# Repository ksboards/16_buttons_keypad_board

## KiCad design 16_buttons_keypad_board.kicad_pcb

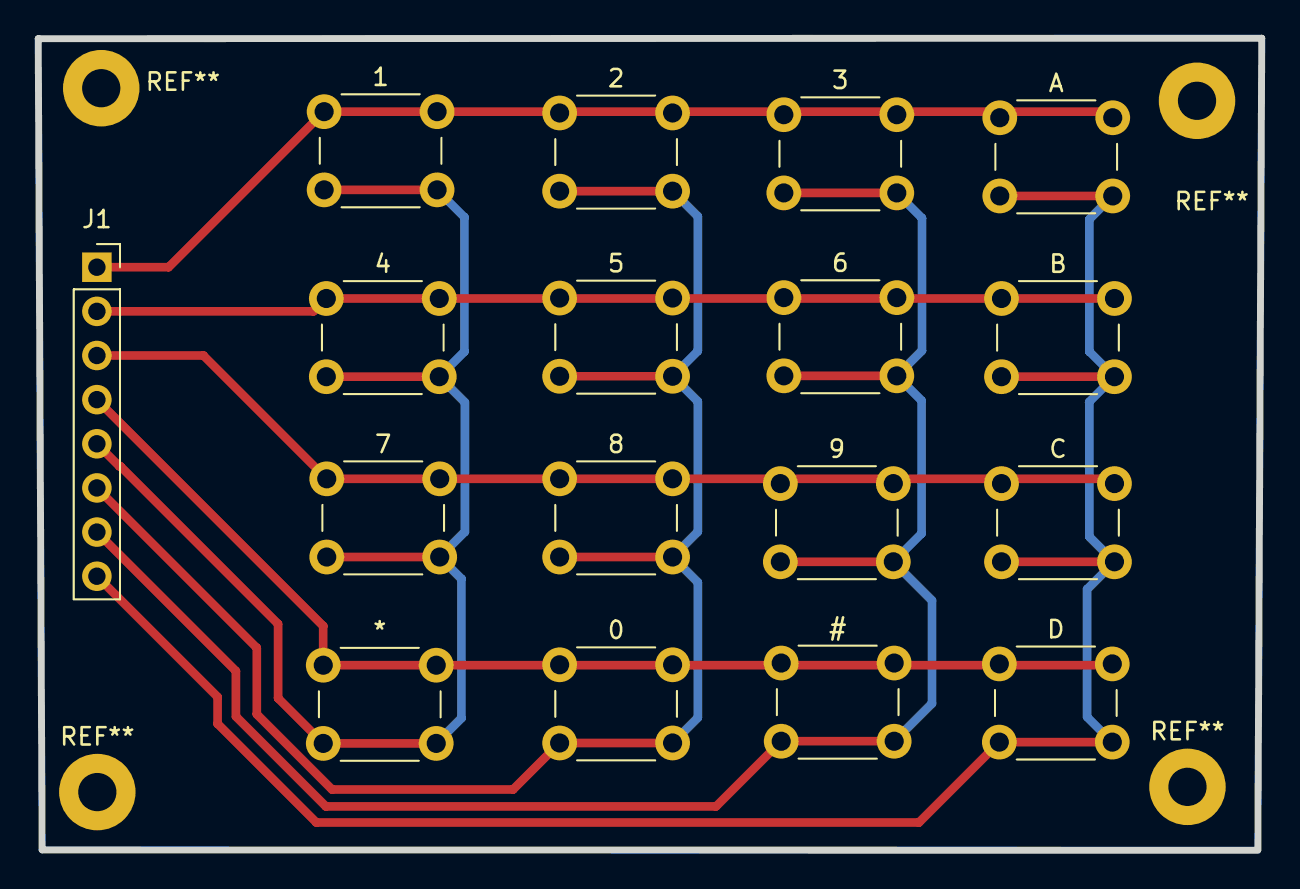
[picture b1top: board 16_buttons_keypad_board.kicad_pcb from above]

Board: 2 copper layers, 70.4 x 46.7 mm, 16 parts (0 on the bottom side), 8 nets.

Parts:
0, 1, 2, 3, 4, 5, 6, 7, 8, 9: SW_Push; SW_PUSH_6mm
*: SW_Push; SW_PUSH_6mm
A: SW_Push; SW_PUSH_6mm
B: SW_Push; SW_PUSH_6mm
C: SW_Push; SW_PUSH_6mm
D: SW_Push; SW_PUSH_6mm
J1: Conn_01x08; PinSocket_1x08_P2.54mm_Vertical

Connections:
/C1: 1.2, 4.2, 7.2, *.2, J1.5
/C2: 0.2, 2.2, 5.2, 8.2, J1.6
/C3: 3.2, 6.2, 9.2, J1.7
/C4: A.2, B.2, C.2, D.2, J1.8
/R1: 1.1, 2.1, 3.1, A.1, J1.1
/R2: 4.1, 5.1, 6.1, B.1, J1.2
/R3: 7.1, 8.1, 9.1, C.1, J1.3
/R4: 0.1, *.1, D.1, J1.4

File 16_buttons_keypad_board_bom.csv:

"Id";"Référence";"Boîtier";"Quantité";"Désignation";"Fournisseur et réf";
1;"REF**,REF**,REF**,REF**";"MountingHole_2.2mm_M2_Pad";4;"MountingHole_2.2mm_M2_Pad";;;
2;"D,C,B,A,#,9,6,3,0,8,5,2,*,7,4,1";"SW_PUSH_6mm";16;"SW_Push";;;
3;"J1";"PinSocket_1x08_P2.54mm_Vertical";1;"Conn_01x08";;;
